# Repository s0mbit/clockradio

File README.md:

# clockradio
Repository for a clock radio ece 299

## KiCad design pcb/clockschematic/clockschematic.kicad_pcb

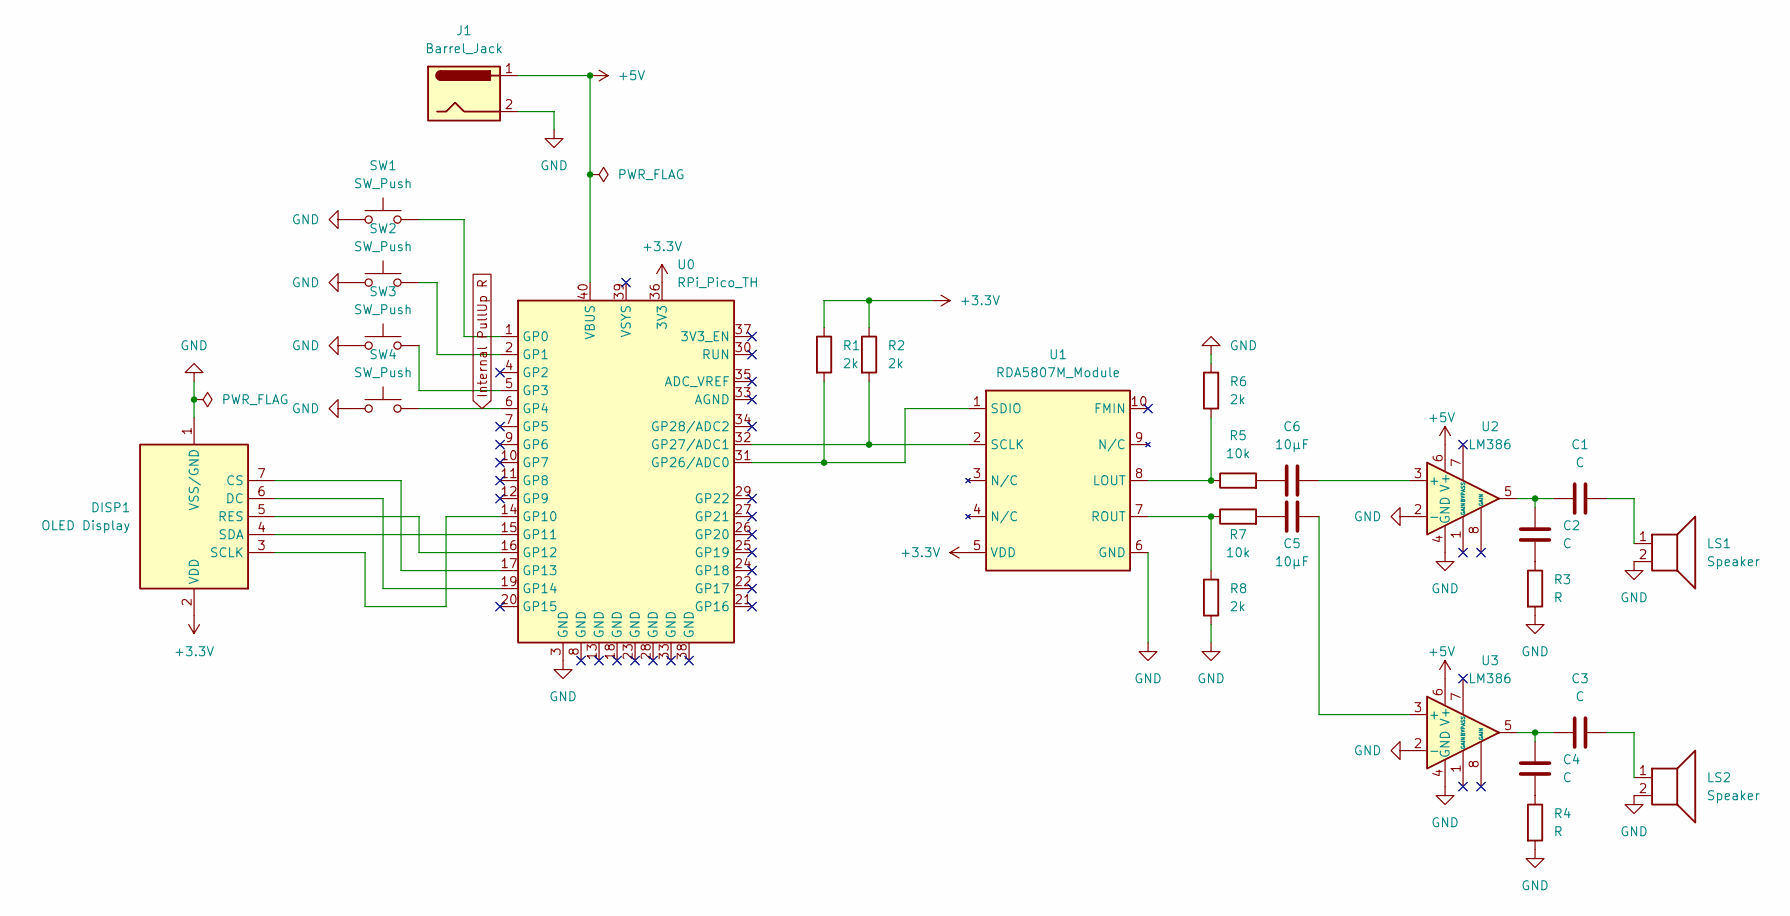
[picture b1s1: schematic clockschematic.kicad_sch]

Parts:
C1, C2, C3, C4: C; CP_Radial_D4.0mm_P2.00mm
C5, C6: 10µF; CP_Radial_D4.0mm_P2.00mm
DISP1: OLED Display; OLED_Display_1.3
J1: Barrel_Jack; BarrelJack_CUI_PJ-063AH_Horizontal
LS1, LS2: Speaker; CUE_CMA-4544PF-W
R1, R2, R6, R8: 2k; R_Axial_DIN0204_L3.6mm_D1.6mm_P7.62mm_Horizontal
R3, R4: R; R_Axial_DIN0204_L3.6mm_D1.6mm_P7.62mm_Horizontal
R5, R7: 10k; R_Axial_DIN0204_L3.6mm_D1.6mm_P7.62mm_Horizontal
SW1, SW2, SW3, SW4: SW_Push; SW_PUSH_6mm
U0: RPi_Pico_TH
U1: RDA5807M_Module; RDA5807M_Module_TH
U2, U3: LM386; DIP08

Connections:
+3.3V: DISP1.2 (VDD), R1.1, R2.1, U0.36 (3V3), U1.5 (VDD)
+5V: J1.1, U0.40 (VBUS), U2.6 (V+), U3.6 (V+)
GND: DISP1.1 (VSS/GND), J1.2, LS1.2, LS2.2, R3.2, R4.2, R6.2, R8.1, SW1.1, SW2.1, SW3.1, SW4.1, U0.3 (GND), U1.6 (GND), U2.2 (-), U2.4 (GND), U3.2 (-), U3.4 (GND)
Internal PullUp R: SW4.2, U0.6 (GP4)
unnamed: C1.1, C2.1, U2.5
unnamed: C1.2, LS1.1
unnamed: C2.2, R3.1
unnamed: C3.1, C4.1, U3.5
unnamed: C3.2, LS2.1
unnamed: C4.2, R4.1
unnamed: DISP1.3 (SCLK), U0.14 (GP10)
unnamed: DISP1.4 (SDA), U0.15 (GP11)
unnamed: DISP1.5 (RES), U0.16 (GP12)
unnamed: DISP1.6 (DC), U0.19 (GP14)
unnamed: DISP1.7 (CS), U0.17 (GP13)
unnamed: R1.2, U0.31 (GP26/ADC0), U1.1 (SDIO)
unnamed: R2.2, U0.32 (GP27/ADC1), U1.2 (SCLK)
unnamed: C6.1, R5.2
unnamed: C5.1, R7.2
unnamed: SW1.2, U0.1 (GP0)
unnamed: SW2.2, U0.2 (GP1)
unnamed: SW3.2, U0.5 (GP3)
unnamed: R7.1, R8.2, U1.7 (ROUT)
unnamed: R5.1, R6.1, U1.8 (LOUT)
unnamed: C6.2, U2.3 (+)
unnamed: C5.2, U3.3 (+)

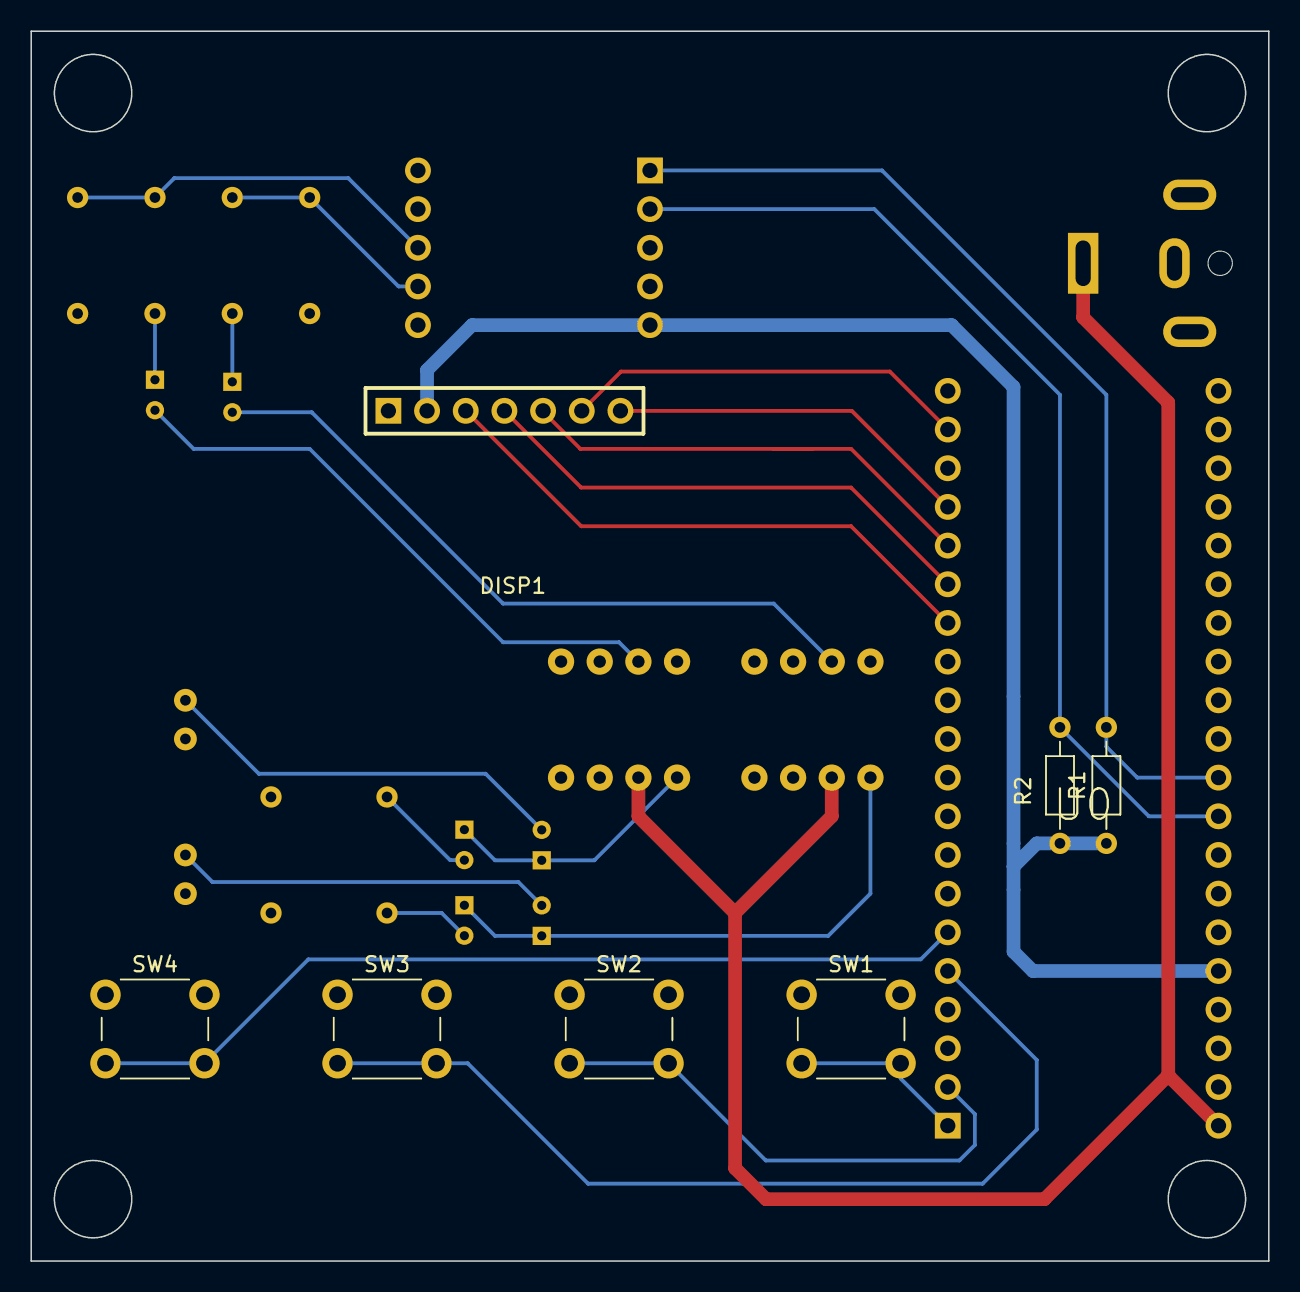
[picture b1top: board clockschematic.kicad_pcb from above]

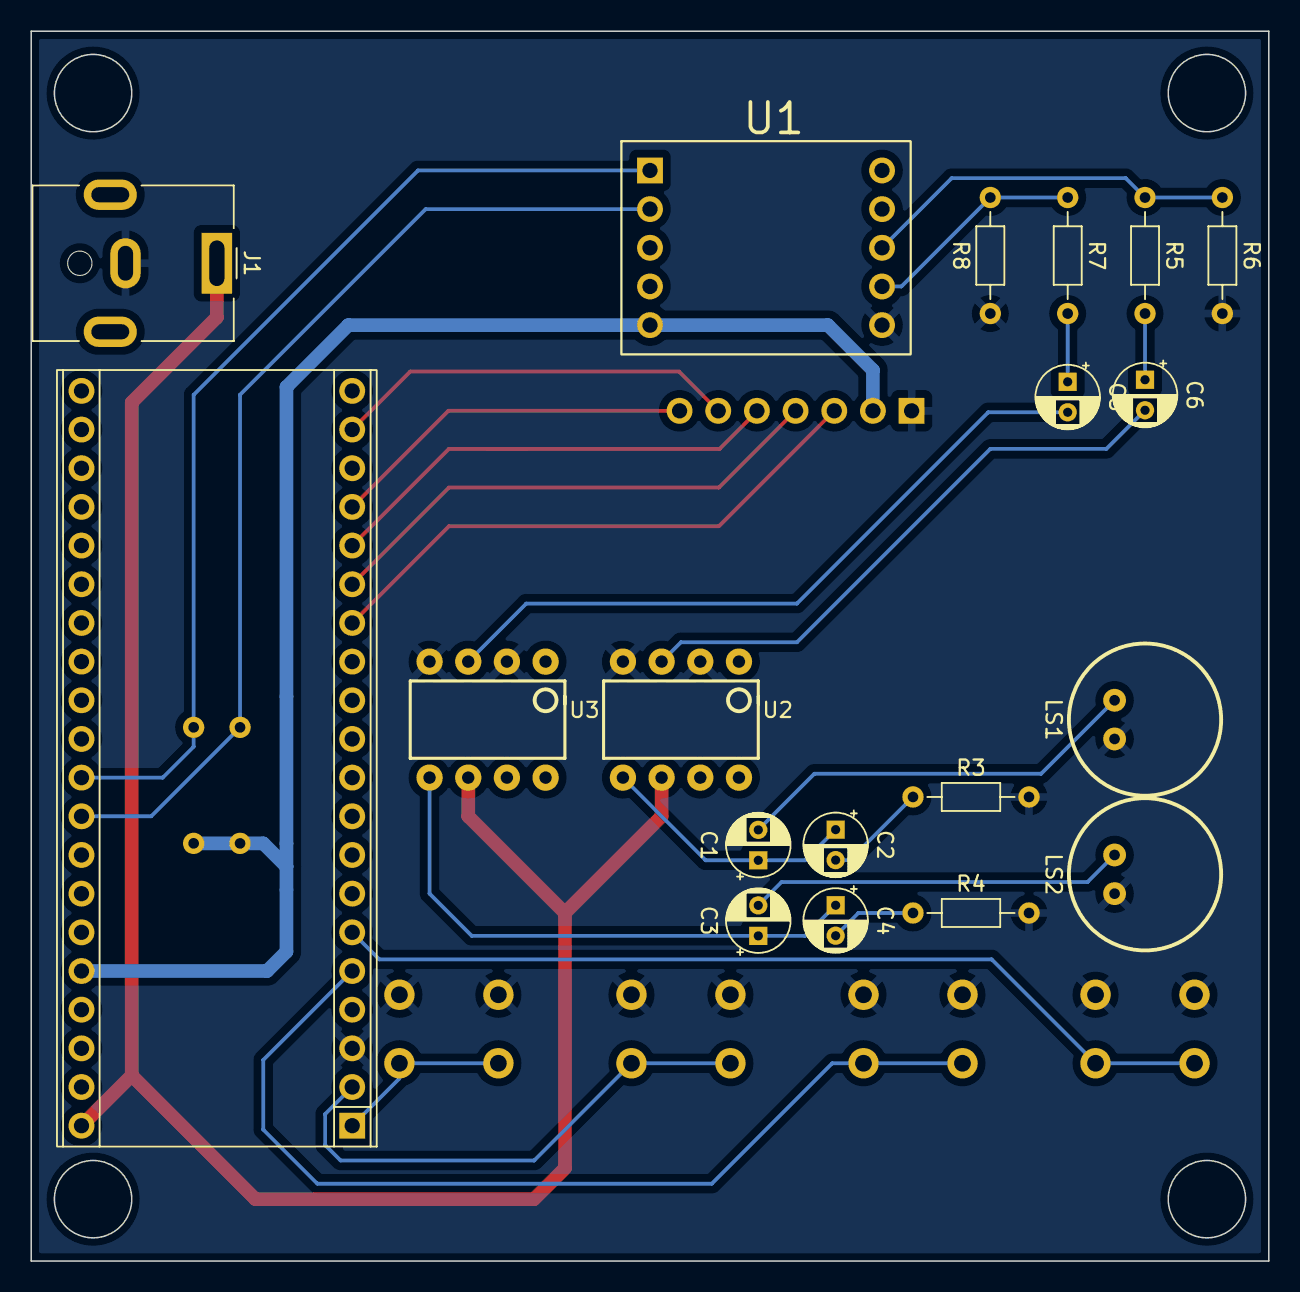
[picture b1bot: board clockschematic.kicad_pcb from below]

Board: 2 copper layers, 81.3 x 80.8 mm, 26 parts (19 on the bottom side), 26 nets.

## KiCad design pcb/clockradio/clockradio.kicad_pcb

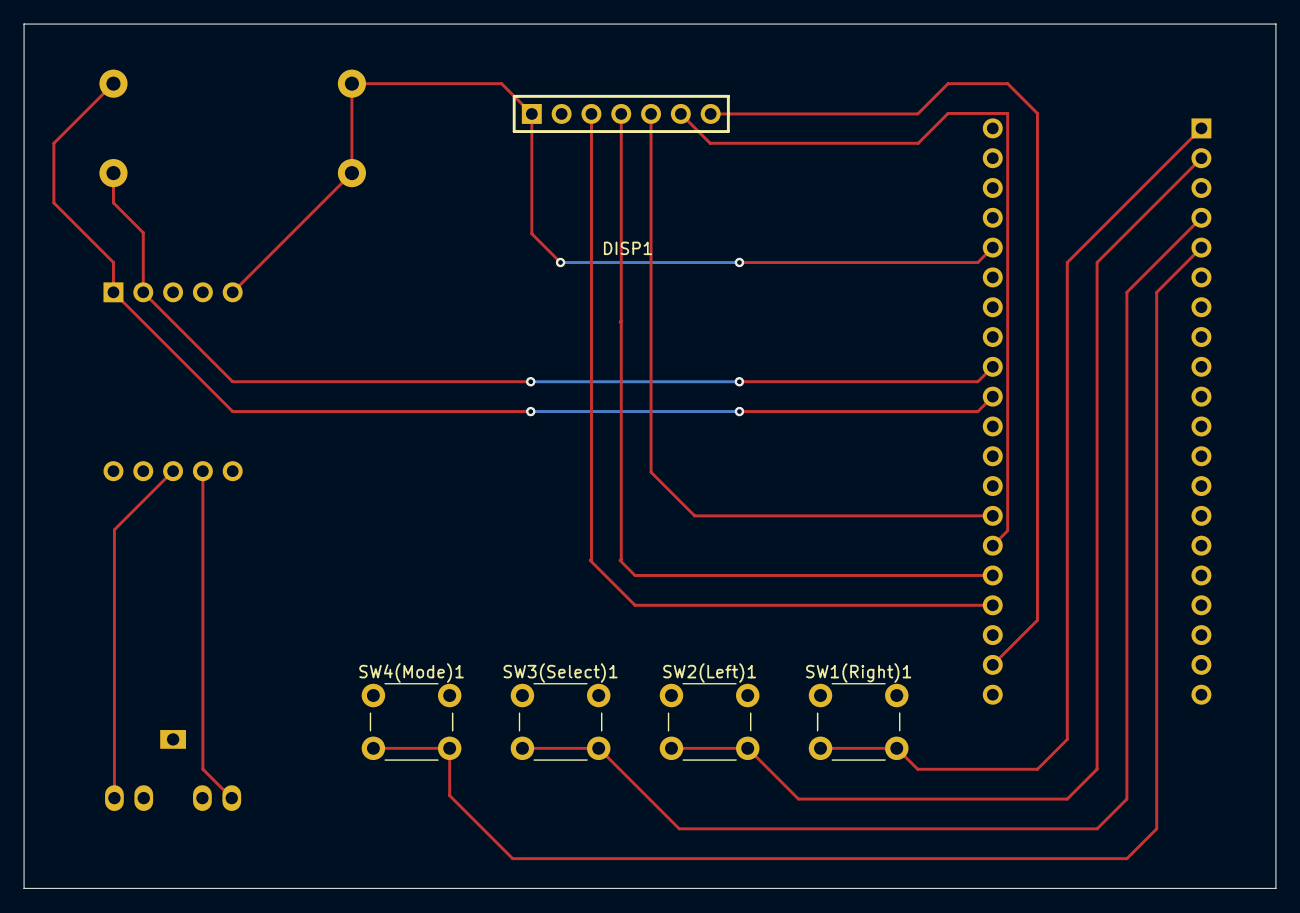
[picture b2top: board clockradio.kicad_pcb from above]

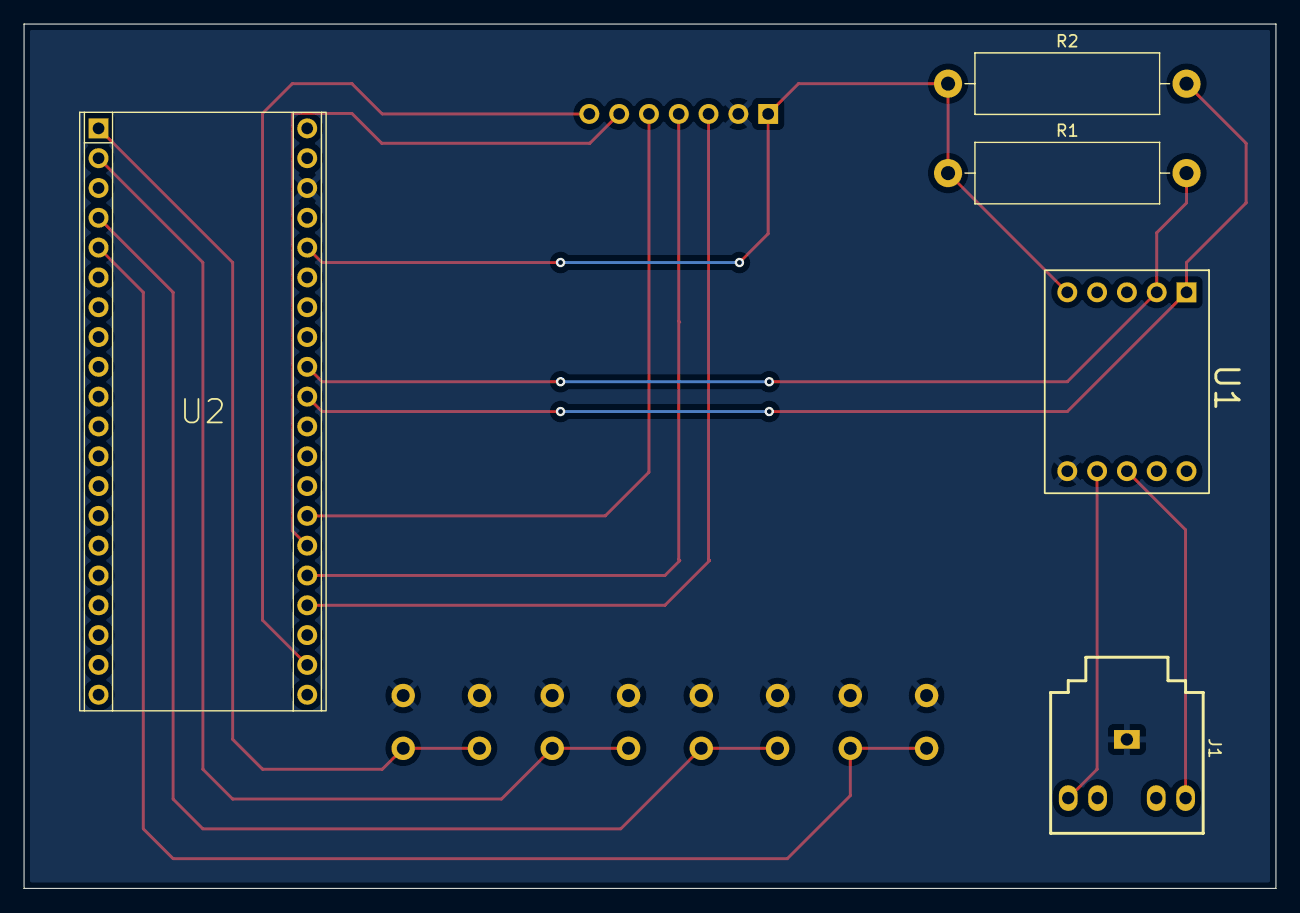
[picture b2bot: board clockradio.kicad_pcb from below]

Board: 2 copper layers, 106.7 x 73.7 mm, 10 parts (5 on the bottom side), 15 nets.

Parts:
DISP1: OLED Display; OLED_Display_1.3
J1: CUE_SJ1-352XNG
R1, R2: 2k; R_Axial_DIN0516_L15.5mm_D5.0mm_P20.32mm_Horizontal
SW1(Right)1, SW2(Left)1, SW3(Select)1, SW4(Mode)1: SW_Push; SW_PUSH_6mm_H8mm
U1: RDA5807M_Module; RDA5807M_Module_TH
U2: RPi_Pico_TH

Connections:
GND: DISP1.2 (VDD), J1.1 (Sleeve), SW1(Right)1.1, SW2(Left)1.1, SW3(Select)1.1, SW4(Mode)1.1, U1.6 (GND), U2.38 (GND)
unnamed: DISP1.3 (SCLK), U2.24 (GP18)
unnamed: DISP1.4 (SDA), U2.25 (GP19)
unnamed: DISP1.5 (RES), U2.27 (GP21)
unnamed: DISP1.6 (DC), U2.26 (GP20)
unnamed: DISP1.7 (CS), U2.22 (GP17)
unnamed: J1.2 (Tip), U1.8 (LOUT)
unnamed: J1.3 (Tip), U1.7 (ROUT)
unnamed: DISP1.1 (VSS/GND), R1.1, R2.1, U1.5 (VDD), U2.36 (3V3)
unnamed: R1.2, U1.2 (SCLK), U2.32 (GP27/ADC1)
unnamed: R2.2, U1.1 (SDIO), U2.31 (GP26/ADC0)
unnamed: SW1(Right)1.2, U2.1 (GP0)
unnamed: SW2(Left)1.2, U2.2 (GP1)
unnamed: SW3(Select)1.2, U2.4 (GP2)
unnamed: SW4(Mode)1.2, U2.5 (GP3)

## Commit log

2023-06-15 added pcb
2023-06-22 installed new lib for display. install it with pip install adafruit-circuitpython-ssd1306
2023-06-22 put the lib in a lib folder for more overview
2023-06-22 made a settings menu for toggeling settings
2023-06-26 added clock functionality
2023-06-27 update pcb
2023-06-30 time is working display is working radio is working new pcb
2023-07-02 finished pcb
2023-07-07 update comments
2023-07-12 updated code n stuff
2023-07-26 Final Update - Everything works
2023-08-02 Finished src and pcb
